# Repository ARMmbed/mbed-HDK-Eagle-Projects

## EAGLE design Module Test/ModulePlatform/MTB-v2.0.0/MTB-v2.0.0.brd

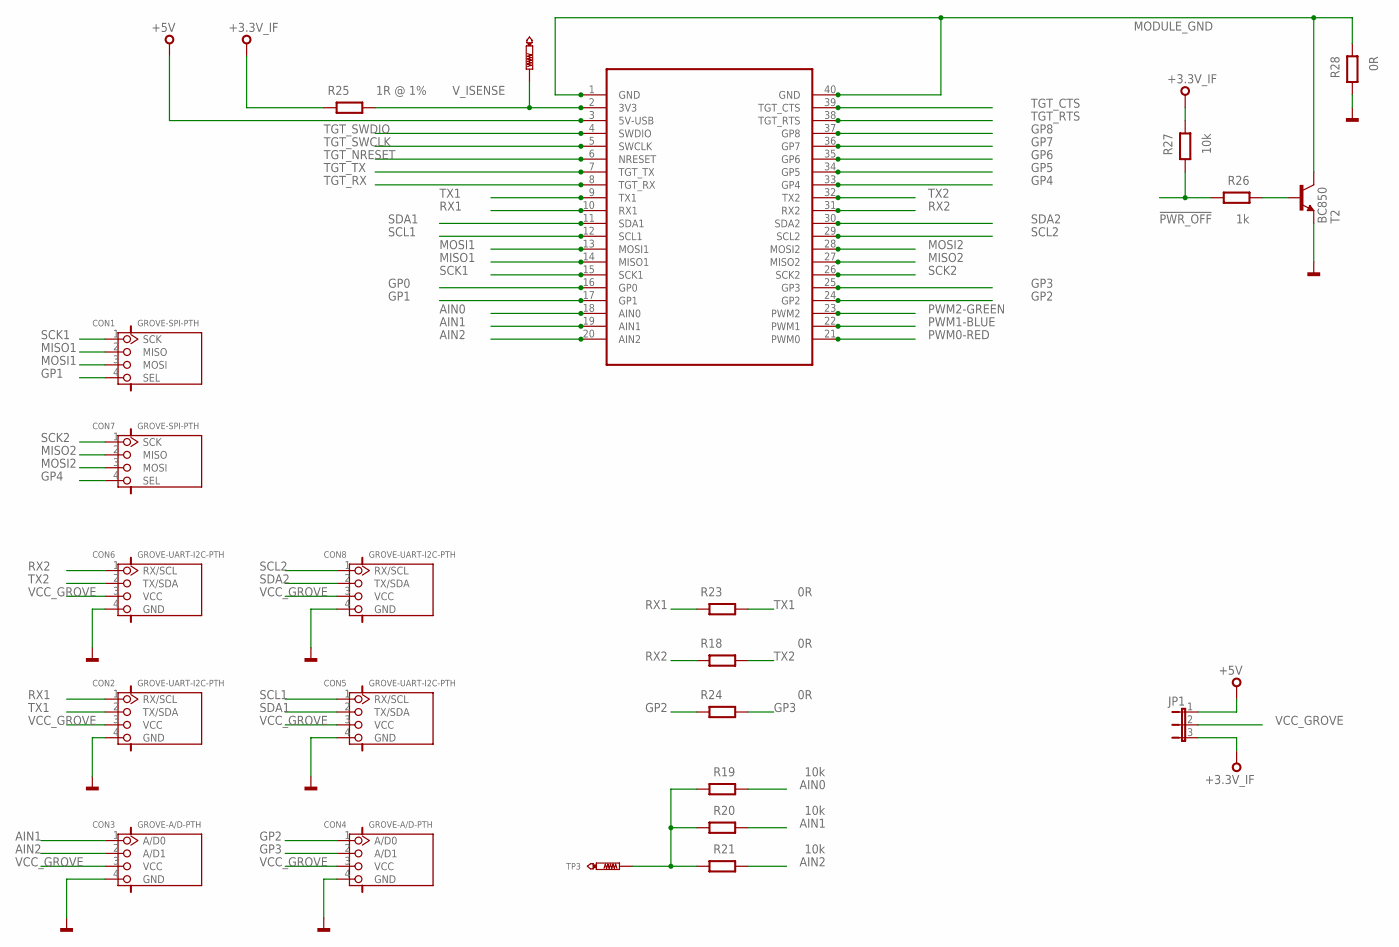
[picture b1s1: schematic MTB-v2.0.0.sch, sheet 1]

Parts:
CON1, CON7: GROVE-SPI-PTH; HW4-2.0
CON2, CON5, CON6, CON8: GROVE-UART-I2C-PTH; HW4-2.0
CON3, CON4: GROVE-A/D-PTH; HW4-2.0
JP1: JP2E; JP2
R18, R23, R24, R28: 0R; 0603@1
R19, R20, R21, R27: 10k; 0603@1
R25: 1R @ 1%; 0603@1
R26: 1k; 0603@1
SKT1: MODULE_SOCKET
T2: BC850; SOT23
TP3: TEST-POINT-50R-PTH; TP50-PTH
TP8: PTR1TP07R; TP07R

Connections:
!PWR_OFF: R26.2, R27.2
+3.3V_IF: JP1.3, R25.2, R27.1; also elsewhere on the board
+5V: JP1.1, SKT1.3 (5V-USB), SKT1.P$43; also elsewhere on the board
AIN0: R19.1, SKT1.18 (AIN0), SKT1.P$58; also elsewhere on the board
AIN1: CON3.1 (A/D0), R20.1, SKT1.19 (AIN1), SKT1.P$59
AIN2: CON3.2 (A/D1), R21.1, SKT1.20 (AIN2), SKT1.P$60
GND: CON2.4 (GND), CON3.4 (GND), CON4.4 (GND), CON5.4 (GND), CON6.4 (GND), CON8.4 (GND), R28.2, T2.2 (E); also elsewhere on the board
GP0: SKT1.16 (GP0), SKT1.P$56; also elsewhere on the board
GP1: CON1.4 (SEL), SKT1.17 (GP1), SKT1.P$57
GP2: CON4.1 (A/D0), R24.2, SKT1.24 (GP2), SKT1.P$64; also elsewhere on the board
GP3: CON4.2 (A/D1), R24.1, SKT1.25 (GP3), SKT1.P$65
GP4: CON7.4 (SEL), SKT1.33 (GP4), SKT1.P$73
GP5: SKT1.34 (GP5), SKT1.P$74; also elsewhere on the board
GP6: SKT1.35 (GP6), SKT1.P$75; also elsewhere on the board
GP7: SKT1.36 (GP7), SKT1.P$76; also elsewhere on the board
GP8: SKT1.37 (GP8), SKT1.P$77
MISO1: CON1.2 (MISO), SKT1.14 (MISO1), SKT1.P$54; also elsewhere on the board
MISO2: CON7.2 (MISO), SKT1.27 (MISO2), SKT1.P$67
MODULE_GND: R28.1, SKT1.1 (GND), SKT1.40 (GND), SKT1.P$41, SKT1.P$80, T2.3 (C)
MOSI1: CON1.3 (MOSI), SKT1.13 (MOSI1), SKT1.P$53; also elsewhere on the board
MOSI2: CON7.3 (MOSI), SKT1.28 (MOSI2), SKT1.P$68
unnamed: R19.2, R20.2, R21.2, TP3.TP
unnamed: R26.1, T2.1 (B)
PWM0-RED: SKT1.21 (PWM0), SKT1.P$61; also elsewhere on the board
PWM1-BLUE: SKT1.22 (PWM1), SKT1.P$62; also elsewhere on the board
PWM2-GREEN: SKT1.23 (PWM2), SKT1.P$63; also elsewhere on the board
RX1: CON2.1 (RX/SCL), R23.2, SKT1.10 (RX1), SKT1.P$50
RX2: CON6.1 (RX/SCL), R18.2, SKT1.31 (RX2), SKT1.P$71
SCK1: CON1.1 (SCK), SKT1.15 (SCK1), SKT1.P$55; also elsewhere on the board
SCK2: CON7.1 (SCK), SKT1.26 (SCK2), SKT1.P$66
SCL1: CON5.1 (RX/SCL), SKT1.12 (SCL1), SKT1.P$52; also elsewhere on the board
SCL2: CON8.1 (RX/SCL), SKT1.29 (SCL2), SKT1.P$69; also elsewhere on the board
SDA1: CON5.2 (TX/SDA), SKT1.11 (SDA1), SKT1.P$51; also elsewhere on the board
SDA2: CON8.2 (TX/SDA), SKT1.30 (SDA2), SKT1.P$70; also elsewhere on the board
TGT_CTS: SKT1.39 (TGT_CTS), SKT1.P$79
TGT_NRESET: SKT1.6 (NRESET), SKT1.P$46; also elsewhere on the board
TGT_RTS: SKT1.38 (TGT_RTS), SKT1.P$78
TGT_RX: SKT1.8 (TGT_RX), SKT1.P$48; also elsewhere on the board
TGT_SWCLK: SKT1.5 (SWCLK), SKT1.P$45; also elsewhere on the board
TGT_SWDIO: SKT1.4 (SWDIO), SKT1.P$44; also elsewhere on the board
TGT_TX: SKT1.7 (TGT_TX), SKT1.P$47; also elsewhere on the board
TX1: CON2.2 (TX/SDA), R23.1, SKT1.9 (TX1), SKT1.P$49
TX2: CON6.2 (TX/SDA), R18.1, SKT1.32 (TX2), SKT1.P$72
VCC_GROVE: CON2.3 (VCC), CON3.3 (VCC), CON4.3 (VCC), CON5.3 (VCC), CON6.3 (VCC), CON8.3 (VCC), JP1.2
V_ISENSE: R25.1, SKT1.2 (3V3), SKT1.P$42, TP8.TP; also elsewhere on the board

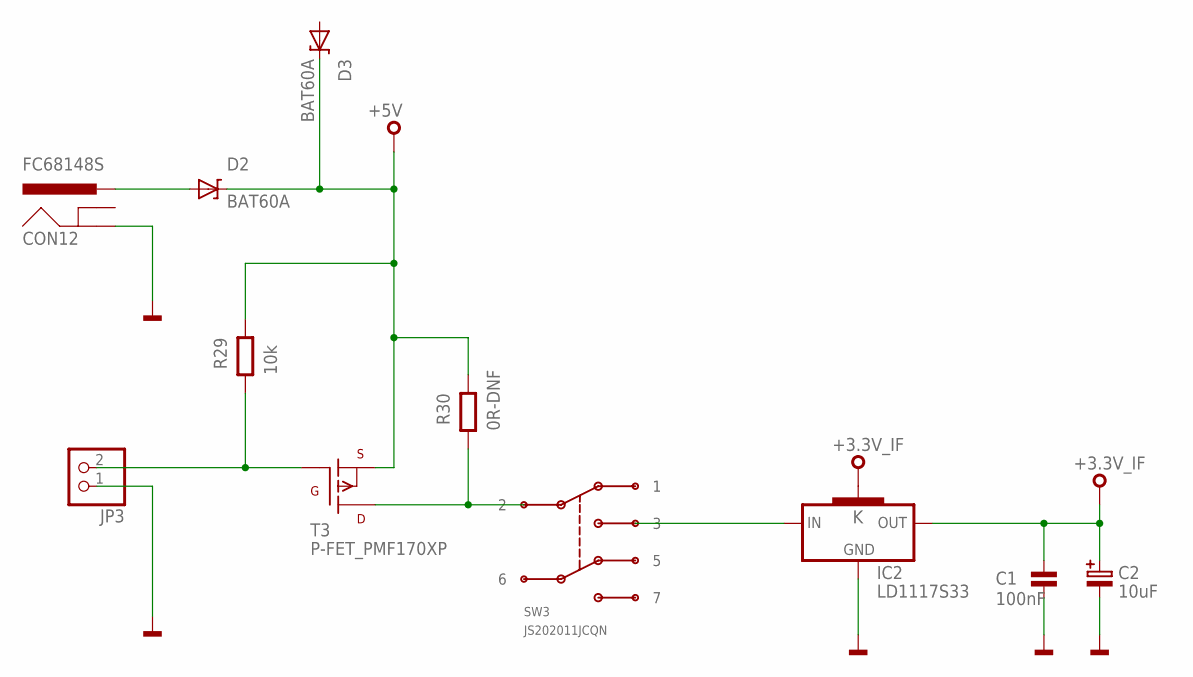
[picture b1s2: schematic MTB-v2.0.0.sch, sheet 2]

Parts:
C1: 100nF; 0603
C2: 10uF; SMC_B
CON12: FC68148S
D2, D3: BAT60A; SOD323
IC2: LD1117S33; SOT223
JP3: PINHD-1X2; 1X02
R29: 10k; 0603@1
R30: 0R-DNF; 0603@1
SW3: JS202011JCQN
T3: P-FET_PMF170XP; SOT23-BEC

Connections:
+3.3V_IF: C1.1, C2.+, IC2.2 (OUT), IC2.4 (K); also elsewhere on the board
+5V: D2.K, D3.K, R29.1, R30.1, T3.E (S); also elsewhere on the board
GND: C1.2, C2.-, CON12.3 (GND), IC2.1 (GND), JP3.1; also elsewhere on the board
unnamed: R30.2, SW3.2, T3.C (D)
unnamed: CON12.1-1 (PWR), CON12.1-2 (PWR), D2.A
unnamed: IC2.3 (IN), SW3.3
unnamed: JP3.2, R29.2, T3.B (G)

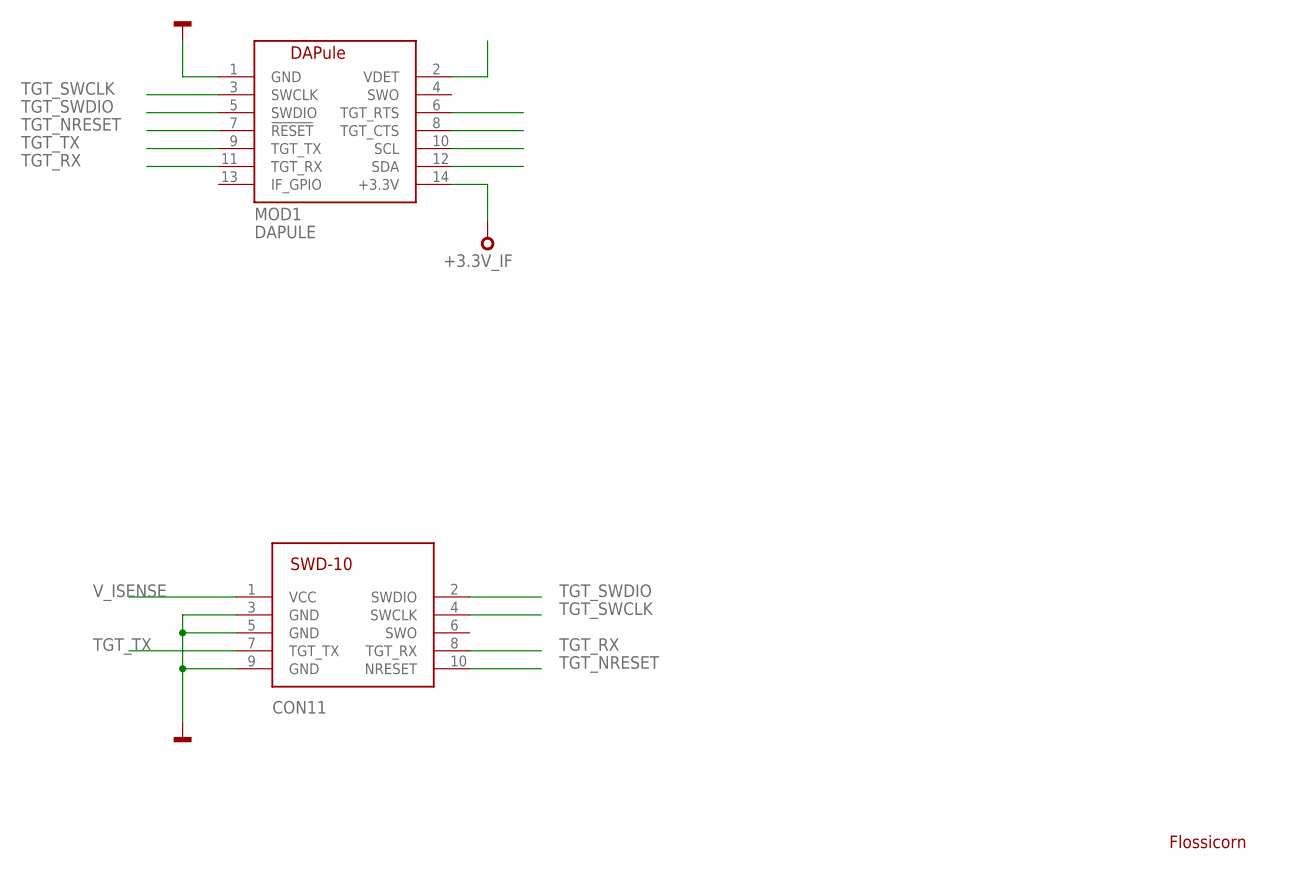
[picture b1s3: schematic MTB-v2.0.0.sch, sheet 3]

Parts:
CON11: SWD-10/TC2050_SMD; FTSH-105-02
MOD1: DAPULE
SS1: FLOSSICORN0.5; FLOSSICORN-0.5

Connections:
+3.3V_IF: MOD1.14 (+3.3V); also elsewhere on the board
GND: CON11.3 (GND), CON11.5 (GND), CON11.9 (GND), MOD1.1 (GND); also elsewhere on the board
TGT_NRESET: CON11.10 (NRESET), MOD1.7 (!RESET); also elsewhere on the board
TGT_RX: CON11.8 (TGT_RX), MOD1.11 (TGT_RX); also elsewhere on the board
TGT_SWCLK: CON11.4 (SWCLK), MOD1.3 (SWCLK); also elsewhere on the board
TGT_SWDIO: CON11.2 (SWDIO), MOD1.5 (SWDIO); also elsewhere on the board
TGT_TX: CON11.7 (TGT_TX), MOD1.9 (TGT_TX); also elsewhere on the board
V_ISENSE: CON11.1 (VCC); also elsewhere on the board

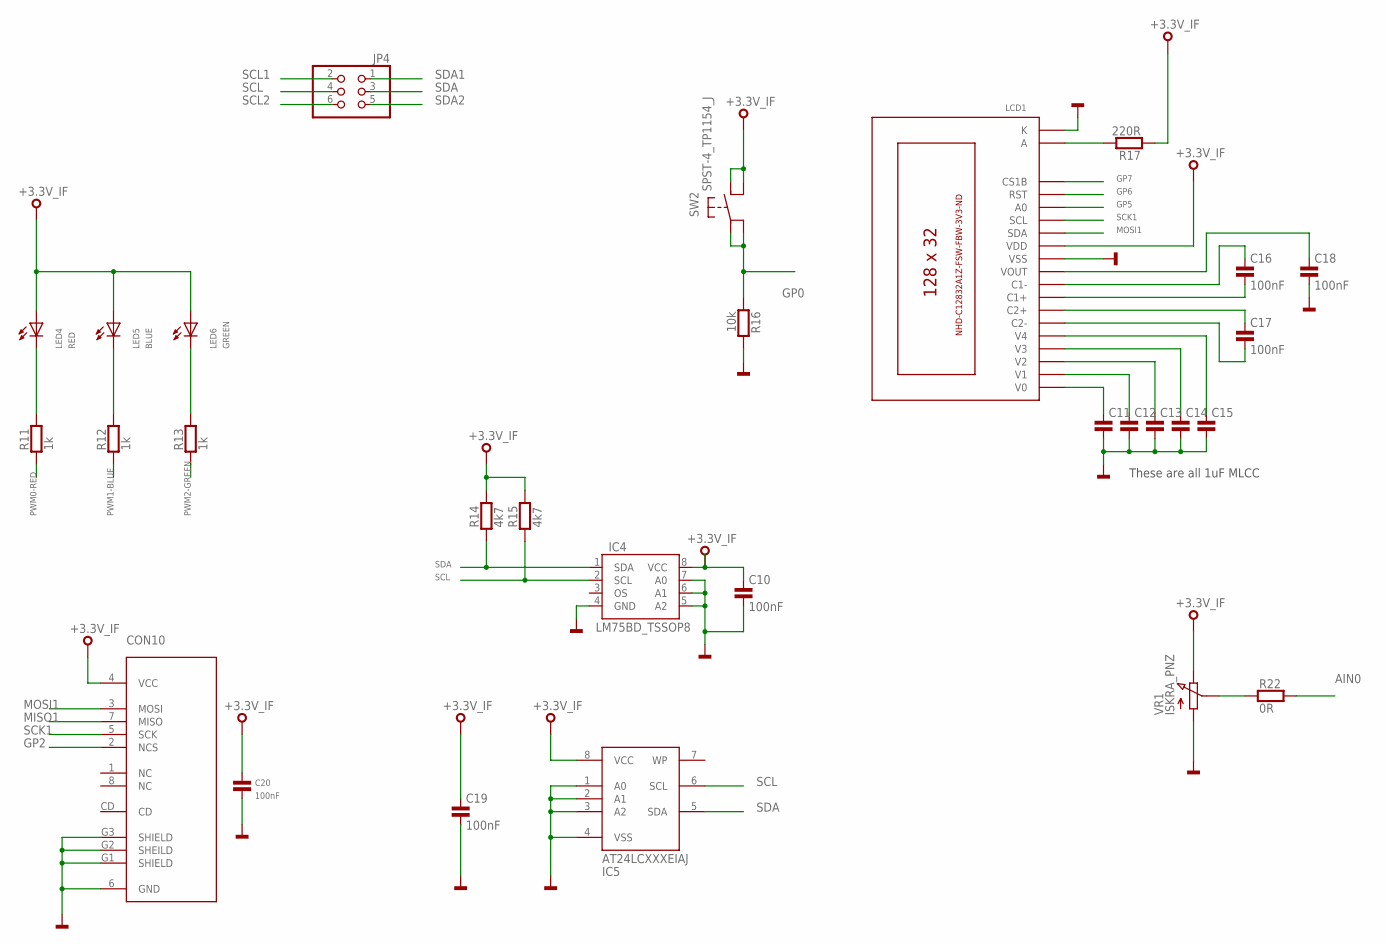
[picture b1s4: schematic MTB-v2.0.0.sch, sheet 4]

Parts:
C10, C11, C12, C13, C14, C15, C16, C17, C18, C19, C20: 100nF; 0603
CON10: MICRO-SD; AMPHENOL-101-00660-68-6
IC4: LM75BD_TSSOP8; TSSOP8
IC5: AT24LCXXXEIAJ; SO08-EIAJ
JP4: PINHD-2X3; 2X03
LCD1: C12832A1Z
LED4: RED; CHIPLED_0603
LED5: BLUE; CHIPLED_0603
LED6: GREEN; CHIPLED_0603
R11, R12, R13: 1k; 0603
R14, R15: 4k7; 0603
R16: 10k; 0603
R17: 220R; 0603
R22: 0R; 0603
SW2: SPST-4_TP1154_J; TP-1154X
VR1: ISKRA_PNZ; CA14V

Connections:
+3.3V_IF: C10.1, C19.1, C20.1, CON10.4 (VCC), IC4.8 (VCC), IC5.8 (VCC), LCD1.P$12 (VDD), LED4.A, LED5.A, LED6.A, R14.2, R15.2, R17.1, SW2.B1, SW2.B2, VR1.P$3 (E); also elsewhere on the board
AIN0: R22.2; also elsewhere on the board
GND: C10.2, C11.2, C12.2, C13.2, C14.2, C15.2, C18.2, C19.2, C20.2, CON10.6 (GND), CON10.G1 (SHIELD), CON10.G2 (SHEILD), CON10.G3 (SHIELD), IC4.4 (GND), IC4.5 (A2), IC4.6 (A1), IC4.7 (A0), IC5.1 (A0), IC5.2 (A1), IC5.3 (A2), IC5.4 (VSS), LCD1.K, LCD1.P$11 (VSS), R16.2, VR1.P$1 (A); also elsewhere on the board
GP0: R16.1, SW2.A1, SW2.A2; also elsewhere on the board
GP2: CON10.2 (NCS); also elsewhere on the board
GP5: LCD1.P$15 (A0); also elsewhere on the board
GP6: LCD1.P$16 (RST); also elsewhere on the board
GP7: LCD1.P$17 (CS1B); also elsewhere on the board
MISO1: CON10.7 (MISO); also elsewhere on the board
MOSI1: CON10.3 (MOSI), LCD1.P$13 (SDA); also elsewhere on the board
unnamed: C16.1, LCD1.P$9 (C1-)
unnamed: C17.1, LCD1.P$7 (C2+)
unnamed: C17.2, LCD1.P$6 (C2-)
unnamed: C16.2, LCD1.P$8 (C1+)
unnamed: C11.1, LCD1.P$1 (V0)
unnamed: C12.1, LCD1.P$2 (V1)
unnamed: C13.1, LCD1.P$3 (V2)
unnamed: C14.1, LCD1.P$4 (V3)
unnamed: C15.1, LCD1.P$5 (V4)
unnamed: C18.1, LCD1.P$10 (VOUT)
unnamed: LED4.C, R11.2
unnamed: LED6.C, R13.2
unnamed: LED5.C, R12.2
unnamed: LCD1.A, R17.2
unnamed: R22.1, VR1.P$2 (S)
PWM0-RED: R11.1; also elsewhere on the board
PWM1-BLUE: R12.1; also elsewhere on the board
PWM2-GREEN: R13.1; also elsewhere on the board
SCK1: CON10.5 (SCK), LCD1.P$14 (SCL); also elsewhere on the board
SCL: IC4.2 (SCL), IC5.6 (SCL), JP4.4, R15.1
SCL1: JP4.2; also elsewhere on the board
SCL2: JP4.6; also elsewhere on the board
SDA: IC4.1 (SDA), IC5.5 (SDA), JP4.3, R14.1
SDA1: JP4.1; also elsewhere on the board
SDA2: JP4.5; also elsewhere on the board

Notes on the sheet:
These are all 1uF MLCC

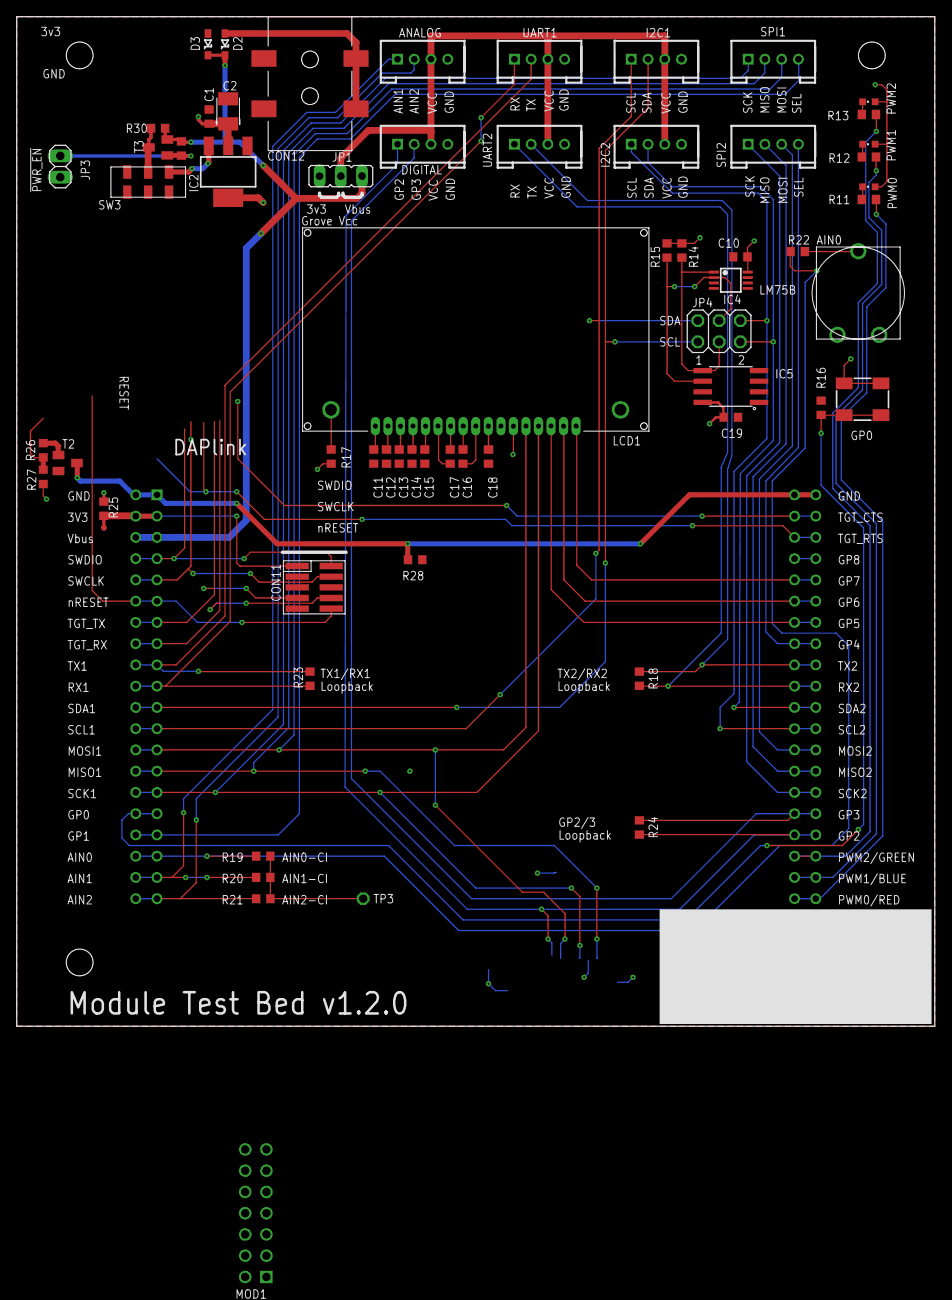
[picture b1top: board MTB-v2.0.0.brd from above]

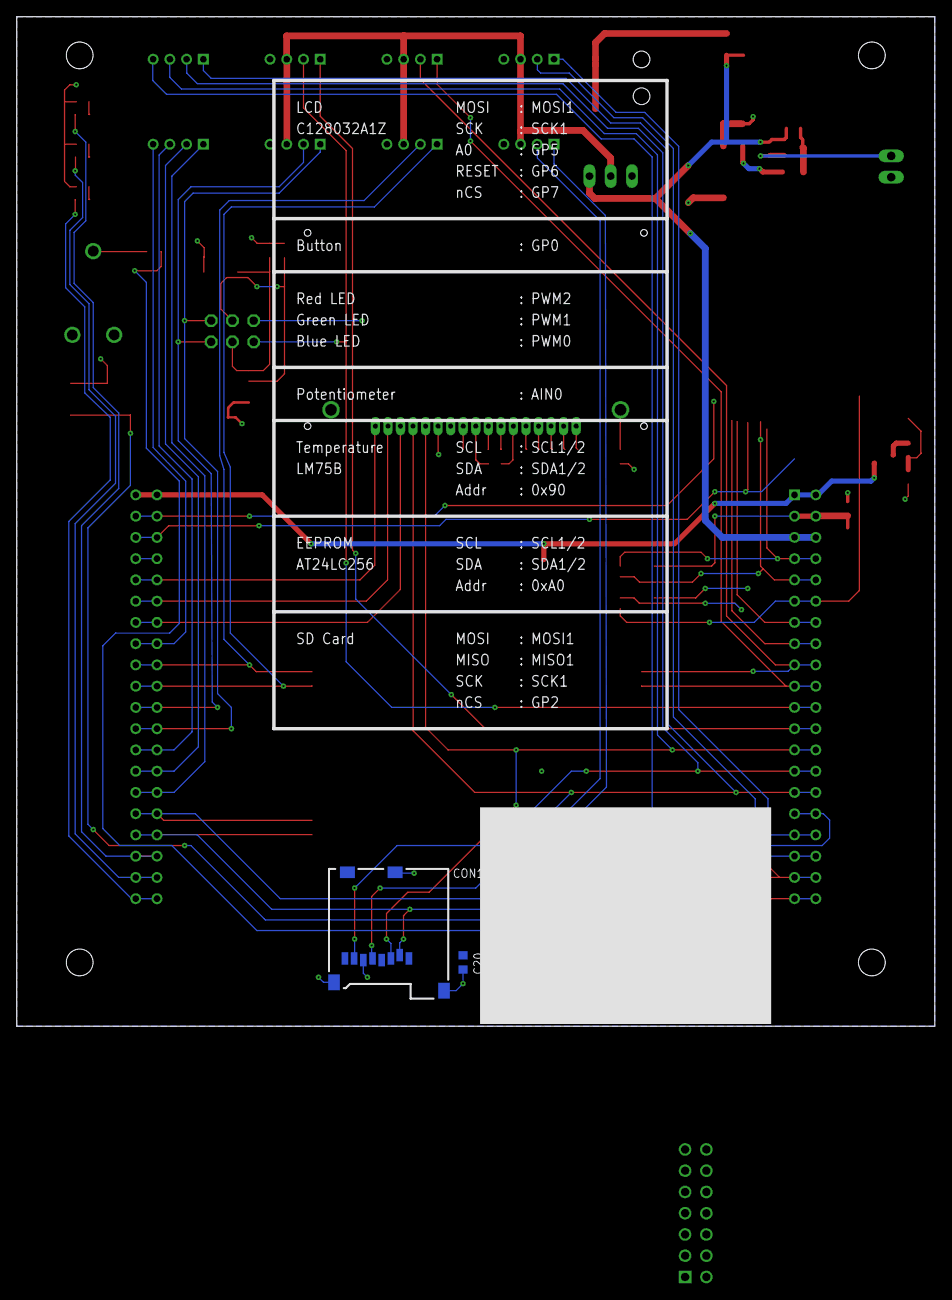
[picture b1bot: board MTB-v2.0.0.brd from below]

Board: 2 copper layers, 109.7 x 120.7 mm, 66 parts (2 on the bottom side), 66 nets.

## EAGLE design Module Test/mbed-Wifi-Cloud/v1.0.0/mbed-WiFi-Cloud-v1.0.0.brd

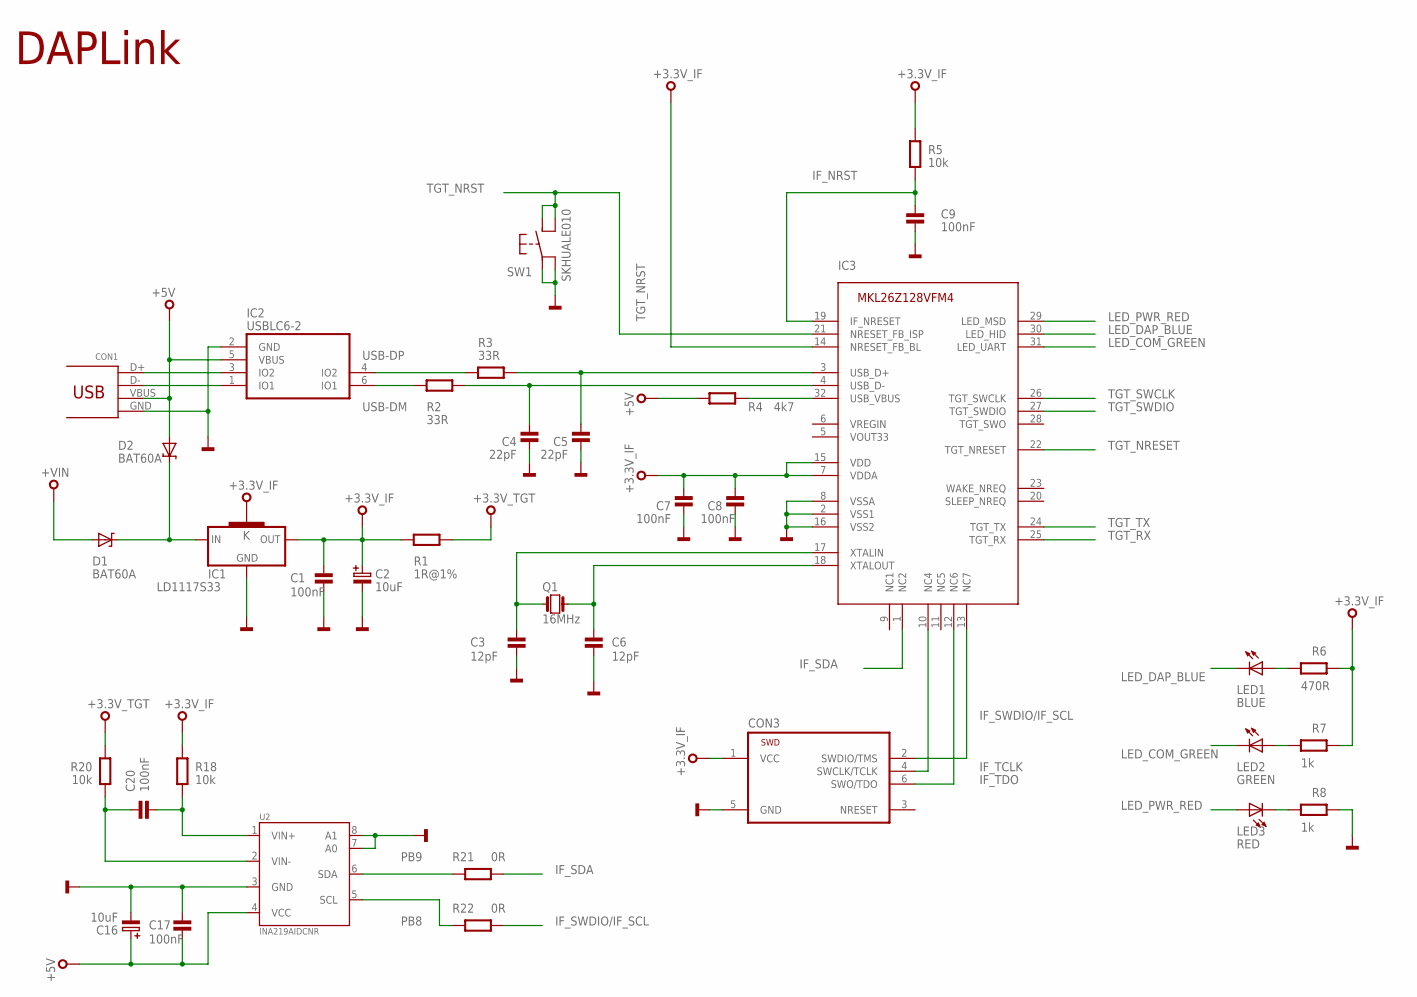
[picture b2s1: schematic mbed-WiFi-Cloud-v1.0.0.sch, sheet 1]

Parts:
C1, C7, C8, C9, C17, C20: 100nF; 0603
C2, C16: 10uF; CASE-B
C3, C6: 12pF; 0603
C4, C5: 22pF; 0603
CON1: USB_MICROB; MOLEX-47364-0001
CON3: TC2030-CTX-NL
D1, D2: BAT60A; SOD323
IC1: LD1117S33; SOT223
IC2: USBLC6-2SC6; SOT23-6L
IC3: IF_MKL26Z128VFM4; HVQFN32
LED1: BLUE; CHIPLED_0603
LED2: GREEN; CHIPLED_0603
LED3: RED; CHIPLED_0603
Q1: 16MHz; 2.5X2.0
R1: 1R@1%; 0603@1
R2, R3: 33R; 0603@1
R4: 4k7; 0603@1
R5, R18, R20: 10k; 0603@1
R6: 470R; 0603@1
R7, R8: 1k; 0603@1
R21, R22: 0R; 0603@1
SW1: SKHUALE010
U2: INA219AIDCNR; SOT23-8

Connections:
+3.3V_IF: C1.1, C2.1, C7.2, C8.2, CON3.1 (VCC), IC1.2 (OUT), IC1.4 (K), IC3.7 (VDDA), IC3.14 (NRESET_FB_BL), IC3.15 (VDD), R1.2, R5.2, R6.1, R7.1, R18.2
+3.3V_TGT: R1.1, R20.2; also elsewhere on the board
+5V: C16.1, C17.2, CON1.VBUS, D2.A, IC2.5 (VBUS), R4.1, U2.4 (VCC); also elsewhere on the board
+VIN: D1.A; also elsewhere on the board
DM: CON1.D-, IC2.1 (IO1)
DP: CON1.D+, IC2.3 (IO2)
GND: C1.2, C2.2, C3.1, C4.1, C5.1, C6.1, C7.1, C8.1, C9.1, C16.2, C17.1, CON1.GND, CON3.5 (GND), IC1.1 (GND), IC2.2 (GND), IC3.2 (VSS1), IC3.8 (VSSA), IC3.16 (VSS2), R8.1, SW1.P$1 (A1), SW1.P$2 (A2), U2.3 (GND), U2.7 (A0), U2.8 (A1); also elsewhere on the board
IF_NRST: C9.2, IC3.19 (IF_NRESET), R5.1
IF_SDA: IC3.1 (NC2), R21.1
IF_SWDIO/IF_SCL: CON3.2 (SWDIO/TMS), IC3.13 (NC7), R22.1
IF_TCLK: CON3.4 (SWCLK/TCLK), IC3.10 (NC4)
IF_TDO: CON3.6 (SWO/TDO), IC3.12 (NC6)
LED_COM_GREEN: IC3.31 (LED_UART), LED2.C
LED_DAP_BLUE: IC3.30 (LED_HID), LED1.C
LED_PWR_RED: IC3.29 (LED_MSD), LED3.A
unnamed: IC3.32 (USB_VBUS), R4.2
unnamed: LED2.A, R7.2
unnamed: C4.2, IC3.4 (USB_D-), R2.1
unnamed: C3.2, IC3.17 (XTALIN), Q1.1
unnamed: D1.K, D2.K, IC1.3 (IN)
unnamed: C6.2, IC3.18 (XTALOUT), Q1.3 (2)
unnamed: LED1.A, R6.2
unnamed: C20.2, R20.1, U2.2 (VIN-)
unnamed: C5.2, IC3.3 (USB_D+), R3.1
unnamed: C20.1, R18.1, U2.1 (VIN+)
unnamed: LED3.C, R8.2
PB8: R22.2, U2.5 (SCL); also elsewhere on the board
PB9: R21.2, U2.6 (SDA); also elsewhere on the board
TGT_NRESET: IC3.22 (TGT_NRESET); also elsewhere on the board
TGT_NRST: IC3.21 (NRESET_FB_ISP), SW1.P$3 (B1), SW1.P$4 (B2)
TGT_RX: IC3.25 (TGT_RX); also elsewhere on the board
TGT_SWCLK: IC3.26 (TGT_SWCLK); also elsewhere on the board
TGT_SWDIO: IC3.27 (TGT_SWDIO); also elsewhere on the board
TGT_TX: IC3.24 (TGT_TX); also elsewhere on the board
USB-DM: IC2.6 (IO1), R2.2
USB-DP: IC2.4 (IO2), R3.2

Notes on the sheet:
DAPLink

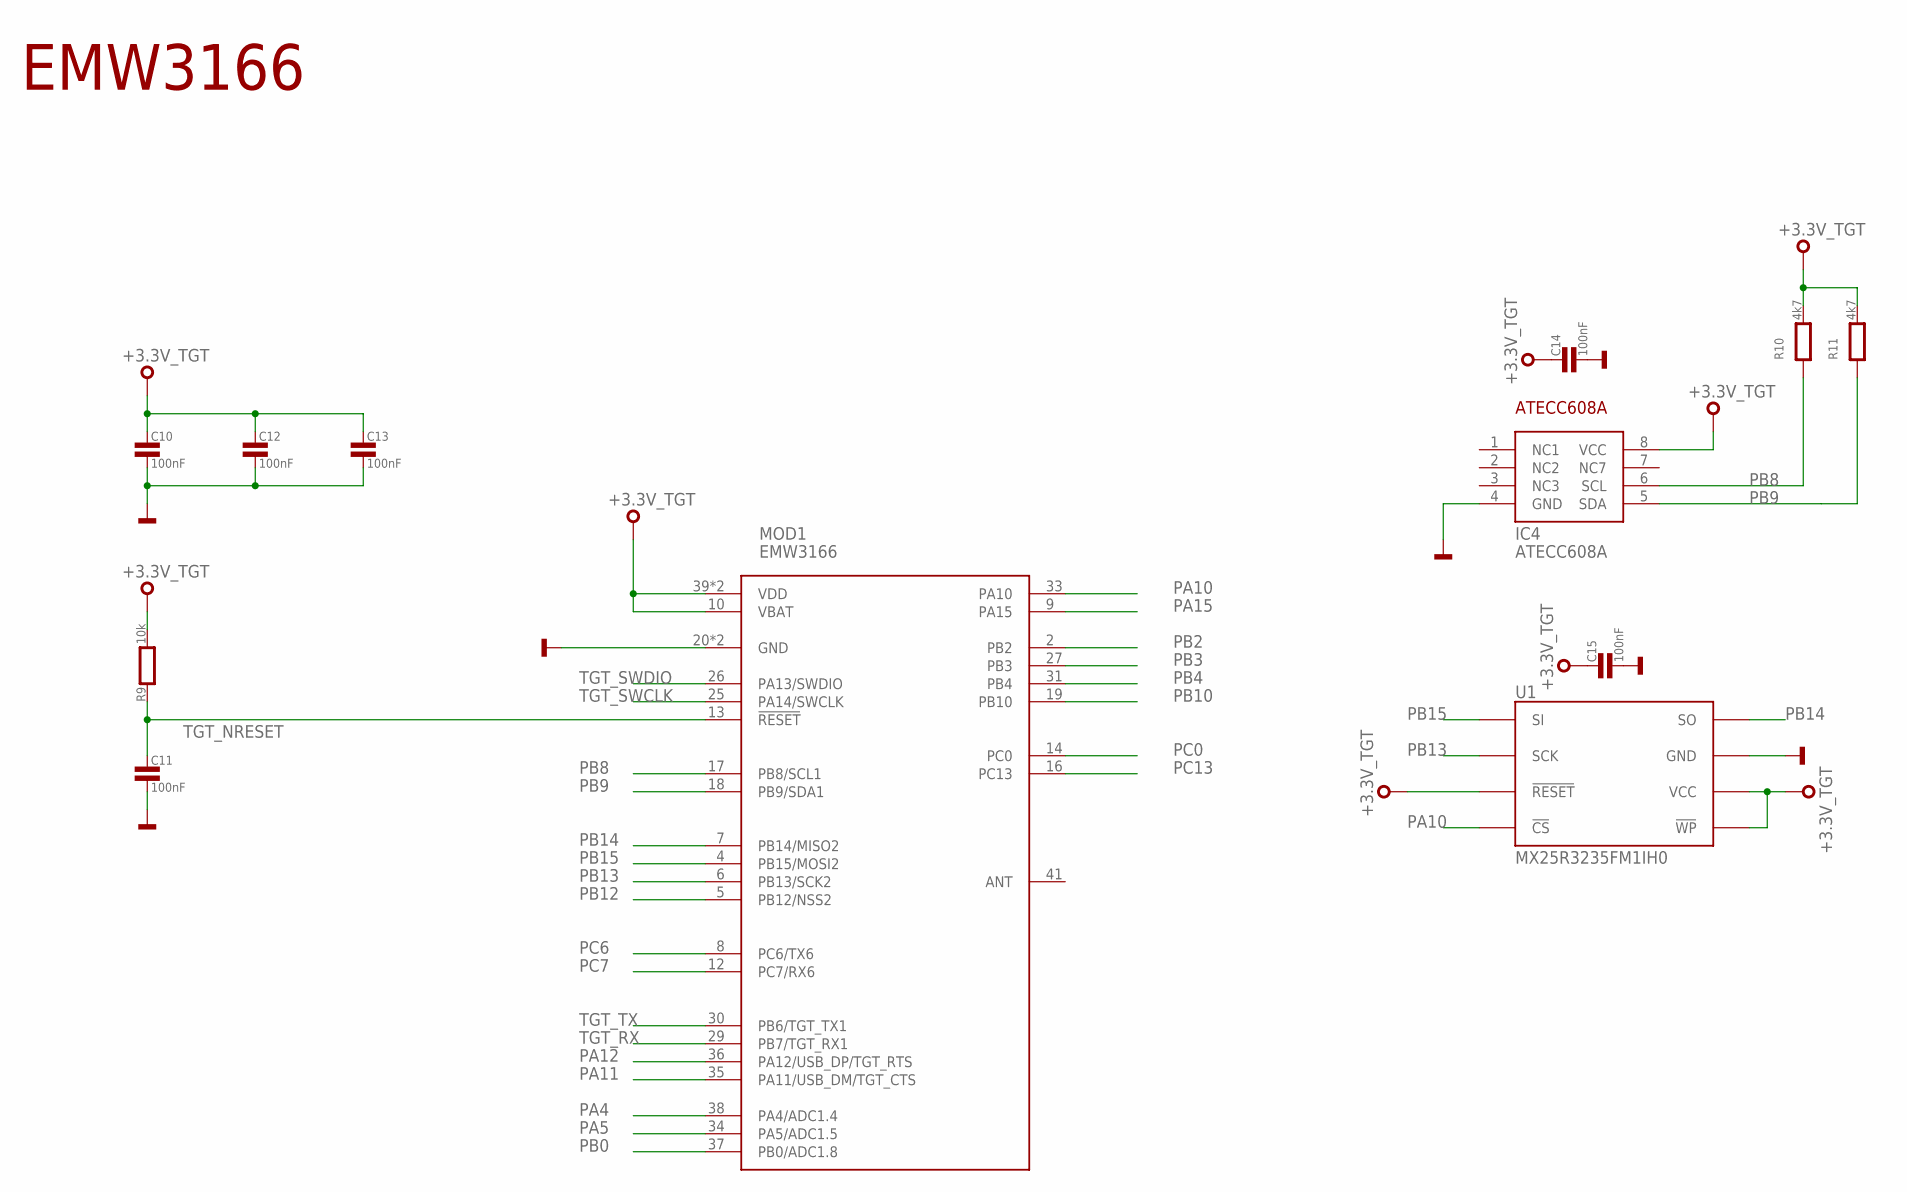
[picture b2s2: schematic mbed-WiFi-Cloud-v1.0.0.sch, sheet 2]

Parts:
C10, C11, C12, C13, C14, C15: 100nF; 0603
IC4: ATECC608A; SO8
MOD1: EMW3166
R9: 10k; 0603
R10, R11: 4k7; 0603
U1: MX25R3235FM1IH0; SO8

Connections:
+3.3V_TGT: C10.1, C12.1, C13.1, C14.1, C15.1, IC4.8 (VCC), MOD1.10 (VBAT), MOD1.39 (VDD), MOD1.40 (VDD), R9.2, R10.2, R11.2, U1.3 (!WP), U1.7 (!RESET), U1.8 (VCC); also elsewhere on the board
GND: C10.2, C11.2, C12.2, C13.2, C14.2, C15.2, IC4.4 (GND), MOD1.20 (GND), MOD1.21 (GND), U1.4 (GND); also elsewhere on the board
PA4: MOD1.38 (PA4/ADC1.4); also elsewhere on the board
PA5: MOD1.34 (PA5/ADC1.5); also elsewhere on the board
PA10: MOD1.33 (PA10), U1.1 (!CS)
PA11: MOD1.35 (PA11/USB_DM/TGT_CTS); also elsewhere on the board
PA12: MOD1.36 (PA12/USB_DP/TGT_RTS); also elsewhere on the board
PA15: MOD1.9 (PA15); also elsewhere on the board
PB0: MOD1.37 (PB0/ADC1.8); also elsewhere on the board
PB2: MOD1.2 (PB2); also elsewhere on the board
PB3: MOD1.27 (PB3); also elsewhere on the board
PB4: MOD1.31 (PB4); also elsewhere on the board
PB8: IC4.6 (SCL), MOD1.17 (PB8/SCL1), R10.1; also elsewhere on the board
PB9: IC4.5 (SDA), MOD1.18 (PB9/SDA1), R11.1; also elsewhere on the board
PB10: MOD1.19 (PB10); also elsewhere on the board
PB12: MOD1.5 (PB12/NSS2); also elsewhere on the board
PB13: MOD1.6 (PB13/SCK2), U1.6 (SCK); also elsewhere on the board
PB14: MOD1.7 (PB14/MISO2), U1.2 (SO); also elsewhere on the board
PB15: MOD1.4 (PB15/MOSI2), U1.5 (SI); also elsewhere on the board
PC0: MOD1.14 (PC0); also elsewhere on the board
PC6: MOD1.8 (PC6/TX6); also elsewhere on the board
PC7: MOD1.12 (PC7/RX6); also elsewhere on the board
PC13: MOD1.16 (PC13); also elsewhere on the board
TGT_NRESET: C11.1, MOD1.13 (!RESET), R9.1; also elsewhere on the board
TGT_RX: MOD1.29 (PB7/TGT_RX1); also elsewhere on the board
TGT_SWCLK: MOD1.25 (PA14/SWCLK); also elsewhere on the board
TGT_SWDIO: MOD1.26 (PA13/SWDIO); also elsewhere on the board
TGT_TX: MOD1.30 (PB6/TGT_TX1); also elsewhere on the board

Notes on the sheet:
EMW3166

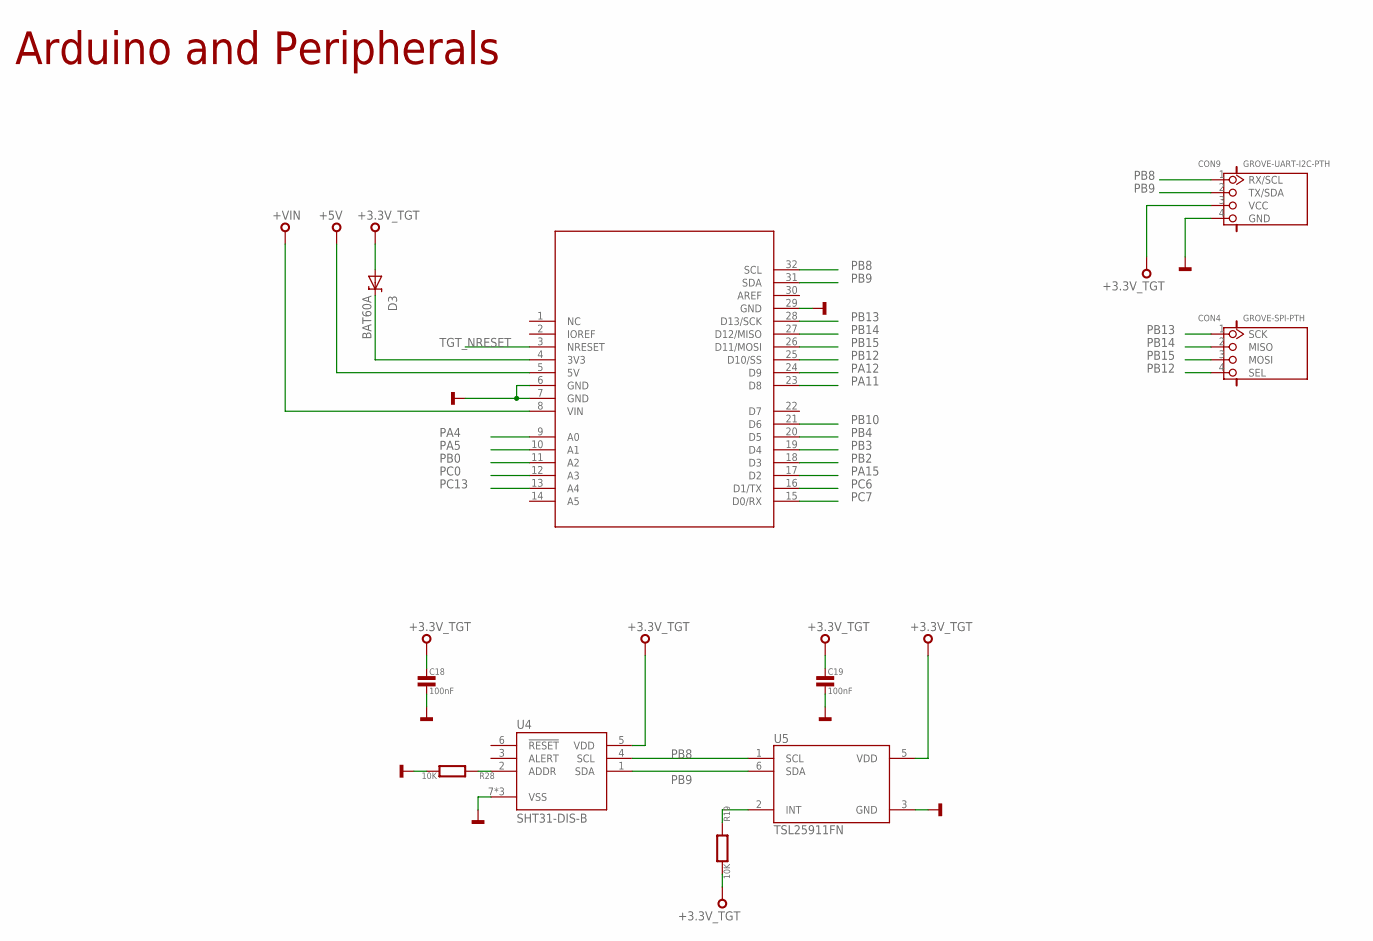
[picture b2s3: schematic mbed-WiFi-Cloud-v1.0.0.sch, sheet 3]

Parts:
BRD1: K64F/K22F-SHIELD; K64F/K22F
C18, C19: 100nF; 0603
CON4: GROVE-SPI-PTH; HW4-2.0
CON9: GROVE-UART-I2C-PTH; HW4-2.0
D3: BAT60A; SOD323
R19, R28: 10K; 0603
U4: SHT31-DIS-B; 8-DFN
U5: TSL25911FN; 6-WFDFN

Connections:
+3.3V_TGT: C18.1, C19.1, CON9.3 (VCC), D3.A, R19.2, U4.5 (VDD), U5.5 (VDD); also elsewhere on the board
+5V: BRD1.5 (5V); also elsewhere on the board
+VIN: BRD1.8 (VIN); also elsewhere on the board
GND: BRD1.6 (GND), BRD1.7 (GND), BRD1.29 (GND), C18.2, C19.2, CON9.4 (GND), R28.2, U4.7 (VSS), U4.8 (VSS), U4.9 (VSS), U5.3 (GND); also elsewhere on the board
unnamed: R28.1, U4.2 (ADDR)
unnamed: BRD1.4 (3V3), D3.K
unnamed: R19.1, U5.2 (INT)
PA4: BRD1.9 (A0); also elsewhere on the board
PA5: BRD1.10 (A1); also elsewhere on the board
PA11: BRD1.23 (D8); also elsewhere on the board
PA12: BRD1.24 (D9); also elsewhere on the board
PA15: BRD1.17 (D2); also elsewhere on the board
PB0: BRD1.11 (A2); also elsewhere on the board
PB2: BRD1.18 (D3); also elsewhere on the board
PB3: BRD1.19 (D4); also elsewhere on the board
PB4: BRD1.20 (D5); also elsewhere on the board
PB8: BRD1.32 (SCL), CON9.1 (RX/SCL), U4.4 (SCL), U5.1 (SCL); also elsewhere on the board
PB9: BRD1.31 (SDA), CON9.2 (TX/SDA), U4.1 (SDA), U5.6 (SDA); also elsewhere on the board
PB10: BRD1.21 (D6); also elsewhere on the board
PB12: BRD1.25 (D10/SS), CON4.4 (SEL); also elsewhere on the board
PB13: BRD1.28 (D13/SCK), CON4.1 (SCK); also elsewhere on the board
PB14: BRD1.27 (D12/MISO), CON4.2 (MISO); also elsewhere on the board
PB15: BRD1.26 (D11/MOSI), CON4.3 (MOSI); also elsewhere on the board
PC0: BRD1.12 (A3); also elsewhere on the board
PC6: BRD1.16 (D1/TX); also elsewhere on the board
PC7: BRD1.15 (D0/RX); also elsewhere on the board
PC13: BRD1.13 (A4); also elsewhere on the board
TGT_NRESET: BRD1.3 (NRESET); also elsewhere on the board

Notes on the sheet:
Arduino and Peripherals

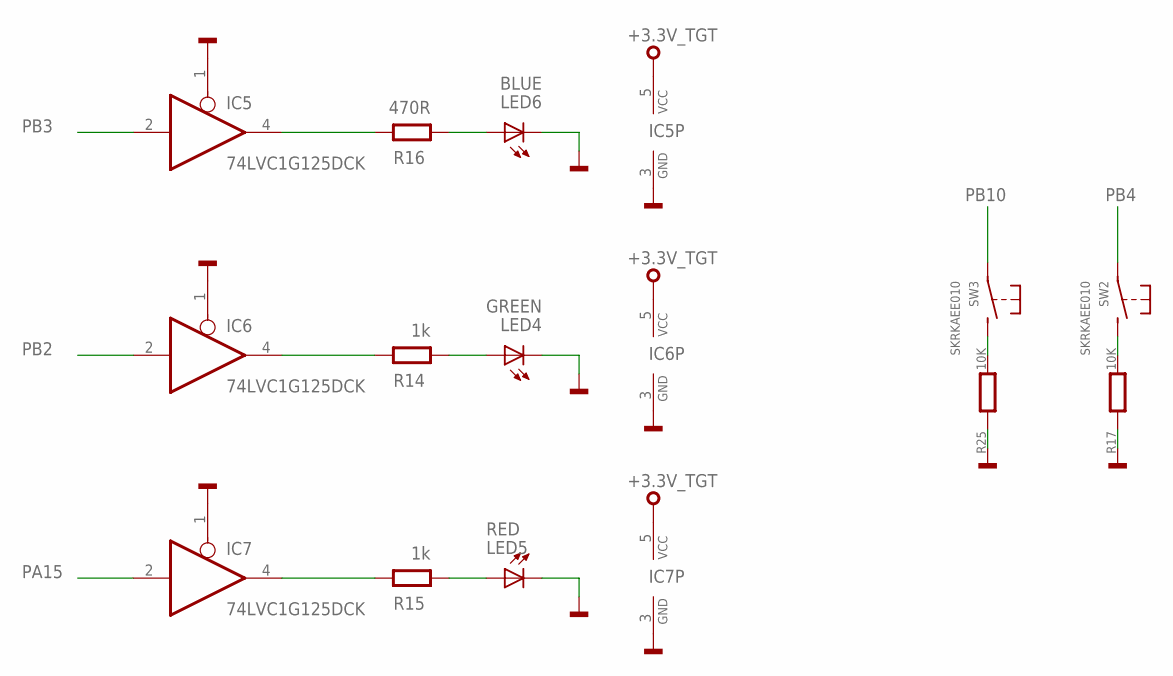
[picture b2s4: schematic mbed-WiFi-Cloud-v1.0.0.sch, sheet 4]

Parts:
IC5, IC6, IC7: 74LVC1G125DCK; SC70-5
LED4: GREEN; CHIPLED_0603
LED5: RED; CHIPLED_0603
LED6: BLUE; CHIPLED_0603
R14, R15: 1k; 0603@1
R16: 470R; 0603@1
R17, R25: 10K; 0603
SW2, SW3: SKRKAEE010

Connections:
+3.3V_TGT: IC5.5 (VCC), IC6.5 (VCC), IC7.5 (VCC); also elsewhere on the board
GND: IC5.1 (OE), IC5.3 (GND), IC6.1 (OE), IC6.3 (GND), IC7.1 (OE), IC7.3 (GND), LED4.C, LED5.C, LED6.C, R17.1, R25.1; also elsewhere on the board
unnamed: LED4.A, R14.2
unnamed: IC7.4 (O), R15.1
unnamed: LED5.A, R15.2
unnamed: IC6.4 (O), R14.1
unnamed: IC5.4 (O), R16.1
unnamed: LED6.A, R16.2
unnamed: R17.2, SW2.P$2 (S)
unnamed: R25.2, SW3.P$2 (S)
PA15: IC7.2 (I); also elsewhere on the board
PB2: IC6.2 (I); also elsewhere on the board
PB3: IC5.2 (I); also elsewhere on the board
PB4: SW2.P$1; also elsewhere on the board
PB10: SW3.P$1; also elsewhere on the board
